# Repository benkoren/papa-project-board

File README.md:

# papa-project-board

This is a universal controller board, centered around the ESP32-C6-DevkitC-1-N8 development board. It is meant to be a solid jumping off point for microcontroller-oriented projects which justify the beefy features of the C6 devkit, including JTAG, 32-bit RISC-V MCU & 2.4 GHz Wi-Fi 6 & Bluetooth 5 (LE) & IEEE 802.15.4, etc.

(TODO: INSERT YOUTUBE DEMO LINK)

## PCB

This universal controller board in particular includes:
 - 1.3" OLED (which you can swap for other sizes as well)
 - (2) 12mm momentary push-button switches
 - rotary encoder switch
 - active buzzer
 - (2) dedicated connectors for 3-pin sensors (ex: DHT-22)
 - (2) dedicated connectors (and extra capacitance) for driving servo motors
 - TBD62783A chip for driving things like relays while protecting our MCU
 - LM2596T-5 voltage regulator that allows the board to be driven by anywhere between 6 and 45 volts (enabling the use of a wide variety of DC power supplies)
 - 10-pin JST-XH connectors are meant to be the primary interface to the usable GPIO pins of the MCU, though extra header pins are included to facilitate tinkering on the benchtop as well
 - 4-pin JSH-XH connector used to extend the I2C devices beyond the included OLED display

For the particular components & footprints, I chose sizes that are easy to install and maintain over the long-term - all Through Hole Technology (THT) components, and no Surface Mount Device (SMD). Silkscreens were heavily utilized so that the user does not need the schematic to populate and maintain the board - all information needed is printed right on the board.

The PCB design was done in KiCad - all relevant files are located in the `KiCad` folder.

The overall approach and many schematic choices borrow a great deal from the [Banano Board by Electro Bananas](https://www.youtube.com/watch?v=pLuV-ciUMUs) - much gratitude goes to him for his work.

## Enclosure

In addition to the PCB design, I've created a corresponding 3d-printed dashplate which allows the board to be incorporated into any surface mount style application.

One such application is the included "Enclosure Y", which is a small enclosure that orients the input components of the controller board up and toward the user, a rear plate where power supply and other connectors are intended to enter, and a bottom-plate which includes a 20mm grid which allows other components to be secured with included mount trays and M3 bolts.

The enclosure design was done in FreeCAD - all relevant files are located in the `FreeCAD` folder.

## Code

Perhaps just as important as the PCB itself is how it's driven: I've created a code template as a great starting point for all projects based upon the universal controller board. It supports some foundational things like driving the OLED and responding to the various inputs included with the board. It's in a separate repository here:

[Papa's Project Board - Code](https://github.com/benkoren/papa-project-board-code)

## Important Changes Across Revisions

### 1.0 to 1.1
 - C11 and C12 are now 0nF - they are counterproductive when using interrupts for SW2 and SW3. We're going to just use software debouncing instead. 
 - R8 is now 470R
 - R5 is now 4.7k (to dim the LED)
 - J7: Both pins 2 and 3 are now connected to GND

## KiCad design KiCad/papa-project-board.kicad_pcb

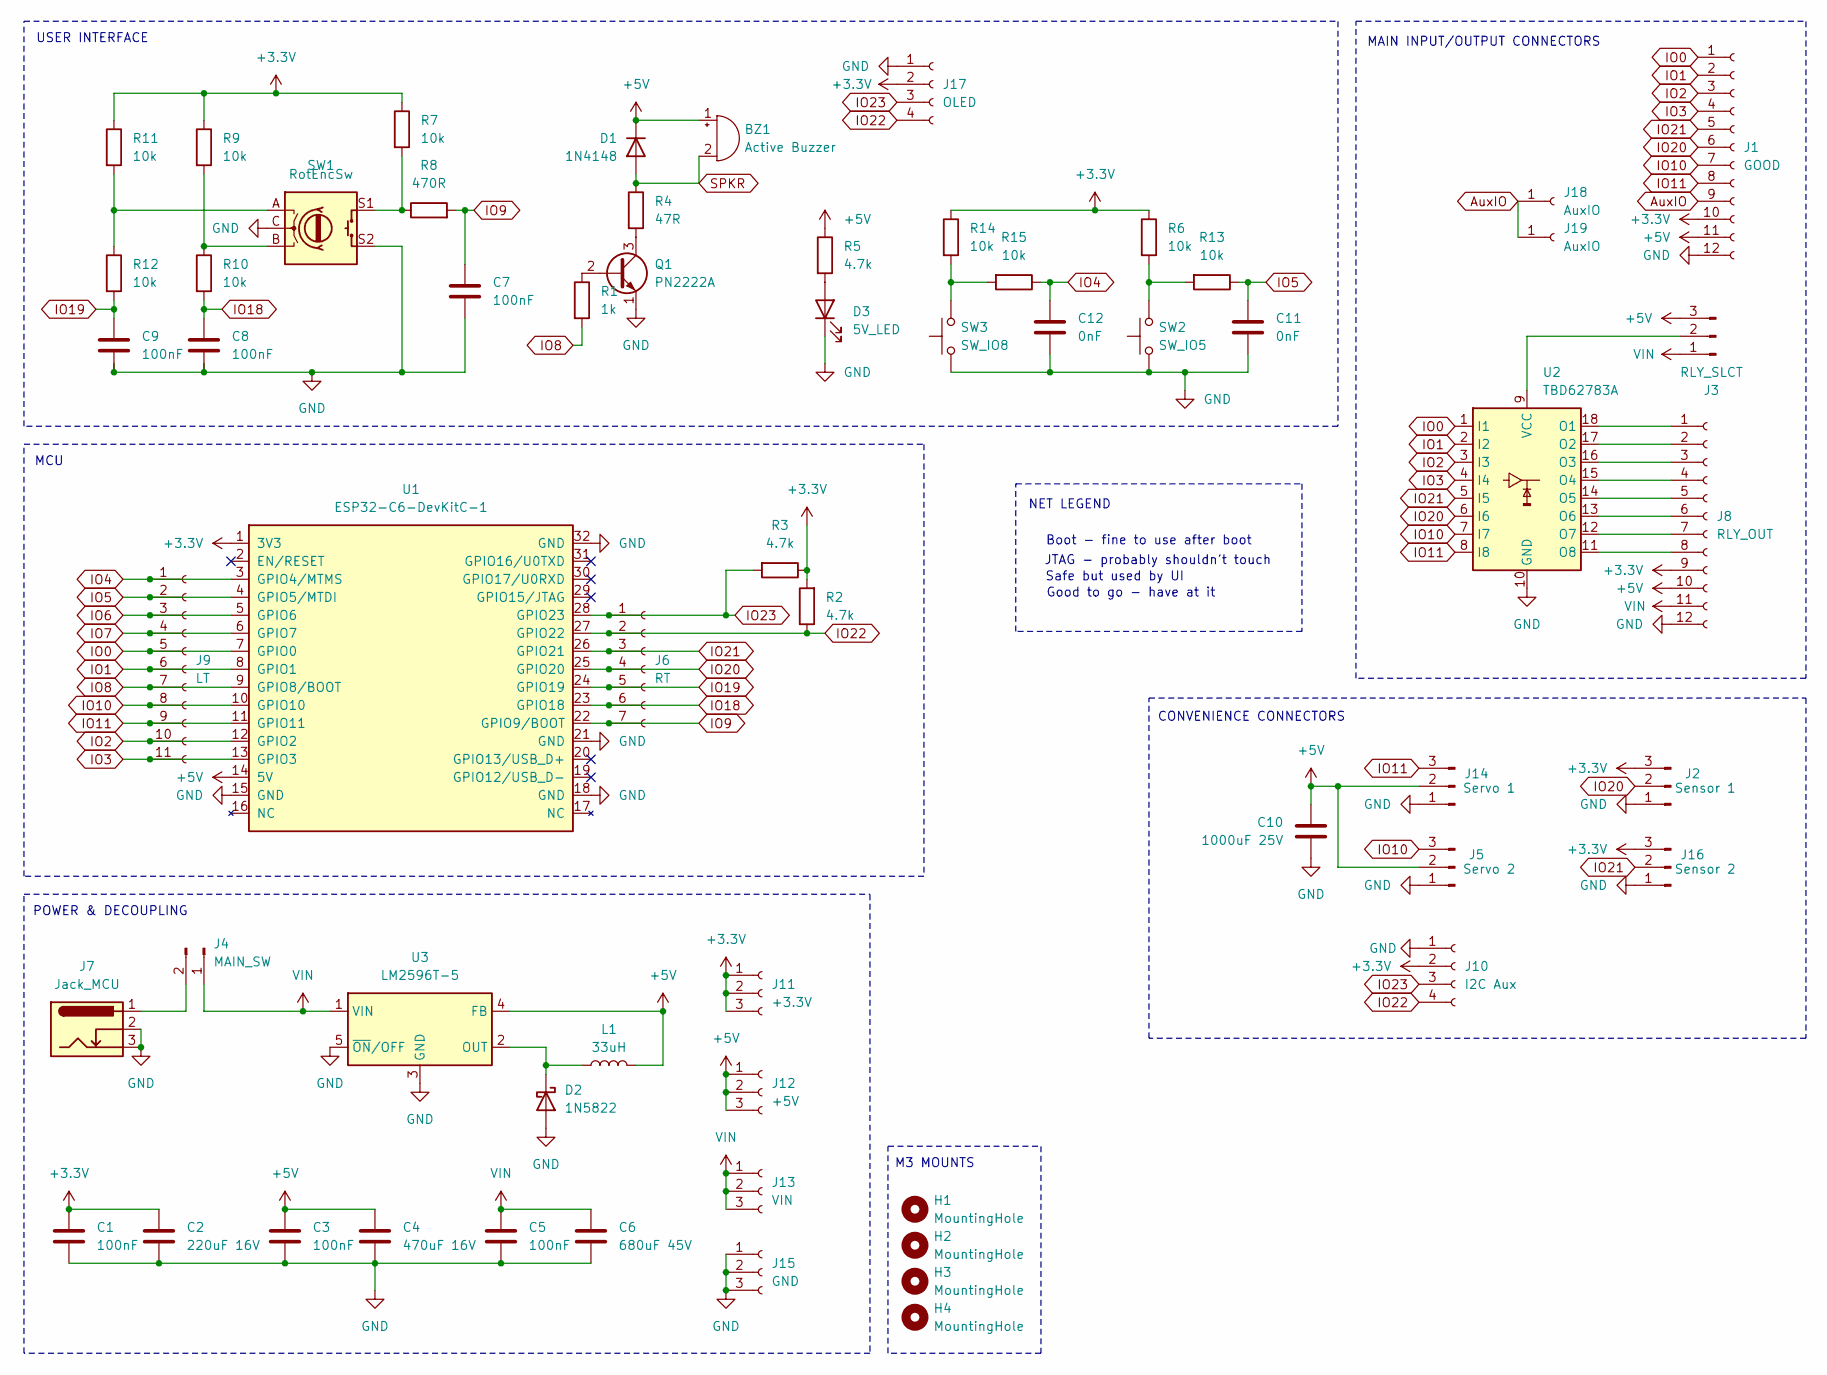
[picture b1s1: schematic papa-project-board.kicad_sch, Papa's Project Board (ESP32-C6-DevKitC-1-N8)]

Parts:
BZ1: Active Buzzer; Buzzer_12x9.5RM7.6
C1, C3, C5, C7, C8, C9: 100nF; C_Disc_D5.0mm_W2.5mm_P5.00mm
C2: 220uF 16V; CP_Radial_D8.0mm_P2.50mm
C4: 470uF 16V; CP_Radial_D8.0mm_P2.50mm
C6: 680uF 45V; CP_Radial_D8.0mm_P2.50mm
C10: 1000uF 25V; CP_Radial_D12.5mm_P5.00mm
C11, C12: 0nF; C_Disc_D5.0mm_W2.5mm_P5.00mm
D1: 1N4148; D_DO-35_SOD27_P7.62mm_Horizontal
D2: 1N5822; D_DO-201AD_P15.24mm_Horizontal
D3: 5V_LED; LED_D5.0mm
H1, H2, H3, H4: MountingHole; MountingHole_3.2mm_M3
J1: GOOD; JST_XH_B12B-XH-A_1x12_P2.50mm_Vertical
J2: Sensor 1; JST_XH_B3B-XH-A_1x03_P2.50mm_Vertical
J3: RLY_SLCT; PinHeader_1x03_P2.54mm_Vertical
J4: MAIN_SW; PinHeader_1x02_P2.54mm_Vertical
J5: Servo 2; JST_XH_B3B-XH-A_1x03_P2.50mm_Vertical
J6: RT; PinSocket_1x07_P2.54mm_Vertical
J7: Jack_MCU; BarrelJack_Horizontal
J8: RLY_OUT; JST_XH_B12B-XH-A_1x12_P2.50mm_Vertical
J9: LT; PinSocket_1x11_P2.54mm_Vertical
J10: I2C Aux; JST_XH_B4B-XH-A_1x04_P2.50mm_Vertical
J11: +3.3V; PinSocket_1x03_P2.54mm_Vertical
J12: +5V; PinSocket_1x03_P2.54mm_Vertical
J13: VIN; PinSocket_1x03_P2.54mm_Vertical
J14: Servo 1; JST_XH_B3B-XH-A_1x03_P2.50mm_Vertical
J15: GND; PinSocket_1x03_P2.54mm_Vertical
J16: Sensor 2; JST_XH_B3B-XH-A_1x03_P2.50mm_Vertical
J17: OLED; PinSocket_1x04_P2.54mm_Vertical
J18, J19: AuxIO; TestPoint_Pad_D1.0mm
L1: 33uH; L_Toroid_Vertical_L14.7mm_W8.6mm_P5.58mm_Pulse_KM-1
Q1: PN2222A; TO-92_Inline
R1: 1k; R_Axial_DIN0207_L6.3mm_D2.5mm_P10.16mm_Horizontal
R2, R3, R5: 4.7k; R_Axial_DIN0207_L6.3mm_D2.5mm_P10.16mm_Horizontal
R4: 47R; R_Axial_DIN0207_L6.3mm_D2.5mm_P10.16mm_Horizontal
R6, R7, R9, R10, R11, R12, R13, R14, R15: 10k; R_Axial_DIN0207_L6.3mm_D2.5mm_P10.16mm_Horizontal
R8: 470R; R_Axial_DIN0207_L6.3mm_D2.5mm_P10.16mm_Horizontal
SW1: RotEncSw; RotaryEncoder_Alps_EC11E-Switch_Vertical_H20mm
SW2: SW_IO5; SW_PUSH-12mm_Wuerth-430476085716
SW3: SW_IO8; SW_PUSH-12mm_Wuerth-430476085716
U1: ESP32-C6-DevKitC-1
U2: TBD62783A; DIP-18_W7.62mm_Socket
U3: LM2596T-5; TO-220-5_Vertical

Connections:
+3.3V: C1.1, C2.1, J1.10, J2.3, J8.9, J10.2, J11.1, J11.2, J11.3, J16.3, J17.2, R2.2, R3.1, R6.1, R7.1, R9.1, R11.1, R14.1, U1.1 (3V3)
+5V: BZ1.1 (+), C3.1, C4.1, C10.1, D1.1 (K), J1.11, J3.3, J5.2, J8.10, J12.1, J12.2, J12.3, J14.2, L1.2, R5.1, U1.14 (5V), U3.4 (FB)
AuxIO: J1.9, J18.1, J19.1
GND: C1.2, C2.2, C3.2, C4.2, C5.2, C6.2, C7.2, C8.2, C9.2, C10.2, C11.2, C12.2, D2.2 (A), D3.1 (K), J1.12, J2.1, J5.1, J7.2, J7.3, J8.12, J10.1, J14.1, J15.1, J15.2, J15.3, J16.1, J17.1, Q1.1 (E), SW1.C, SW1.S2, SW2.1, SW3.1, U1.15 (GND), U1.18 (GND), U1.21 (GND), U1.32 (GND), U2.10 (GND), U3.3 (GND), U3.5 (~ON/OFF)
IO0: J1.1, J9.5, U1.7 (GPIO0), U2.1 (I1)
IO1: J1.2, J9.6, U1.8 (GPIO1), U2.2 (I2)
IO2: J1.3, J9.10, U1.12 (GPIO2), U2.3 (I3)
IO3: J1.4, J9.11, U1.13 (GPIO3), U2.4 (I4)
IO4: C12.1, J9.1, R15.1, U1.3 (GPIO4/MTMS)
IO5: C11.1, J9.2, R13.1, U1.4 (GPIO5/MTDI)
IO6: J9.3, U1.5 (GPIO6)
IO7: J9.4, U1.6 (GPIO7)
IO8: J9.7, R1.2, U1.9 (GPIO8/BOOT)
IO9: C7.1, J6.7, R8.2, U1.22 (GPIO9/BOOT)
IO10: J1.7, J5.3, J9.8, U1.10 (GPIO10), U2.7 (I7)
IO11: J1.8, J9.9, J14.3, U1.11 (GPIO11), U2.8 (I8)
IO18: C8.1, J6.6, R10.2, U1.23 (GPIO18)
IO19: C9.1, J6.5, R12.2, U1.24 (GPIO19)
IO20: J1.6, J2.2, J6.4, U1.25 (GPIO20), U2.6 (I6)
IO21: J1.5, J6.3, J16.2, U1.26 (GPIO21), U2.5 (I5)
IO22: J6.2, J10.4, J17.4, R2.1, U1.27 (GPIO22)
IO23: J6.1, J10.3, J17.3, R3.2, U1.28 (GPIO23)
unnamed: D2.1 (K), L1.1, U3.2 (OUT)
unnamed: D3.2 (A), R5.2
unnamed: J3.2, U2.9 (VCC)
unnamed: J4.2, J7.1
unnamed: J8.1, U2.18 (O1)
unnamed: J8.2, U2.17 (O2)
unnamed: J8.3, U2.16 (O3)
unnamed: J8.4, U2.15 (O4)
unnamed: J8.5, U2.14 (O5)
unnamed: J8.6, U2.13 (O6)
unnamed: J8.7, U2.12 (O7)
unnamed: J8.8, U2.11 (O8)
unnamed: Q1.2 (B), R1.1
unnamed: Q1.3 (C), R4.2
unnamed: R7.2, R8.1, SW1.S1
unnamed: R9.2, R10.1, SW1.B
unnamed: R11.2, R12.1, SW1.A
unnamed: R6.2, R13.2, SW2.2
unnamed: R14.2, R15.2, SW3.2
SPKR: BZ1.2 (-), D1.2 (A), R4.1
VIN: C5.1, C6.1, J3.1, J4.1, J8.11, J13.1, J13.2, J13.3, U3.1 (VIN)

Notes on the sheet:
JTAG - probably shouldn't touch
USER INTERFACE
Boot - fine to use after boot
Good to go - have at it
MAIN INPUT/OUTPUT CONNECTORS
MCU
M3 MOUNTS
Safe but used by UI
NET LEGEND
POWER & DECOUPLING
CONVENIENCE CONNECTORS

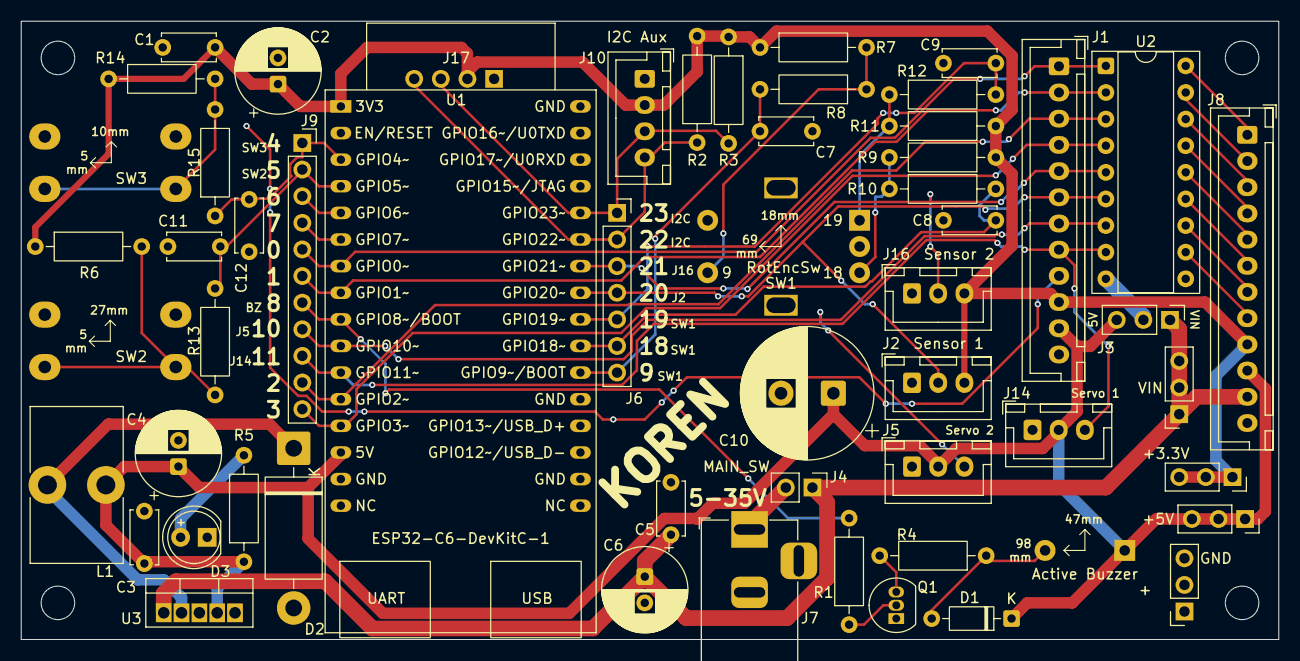
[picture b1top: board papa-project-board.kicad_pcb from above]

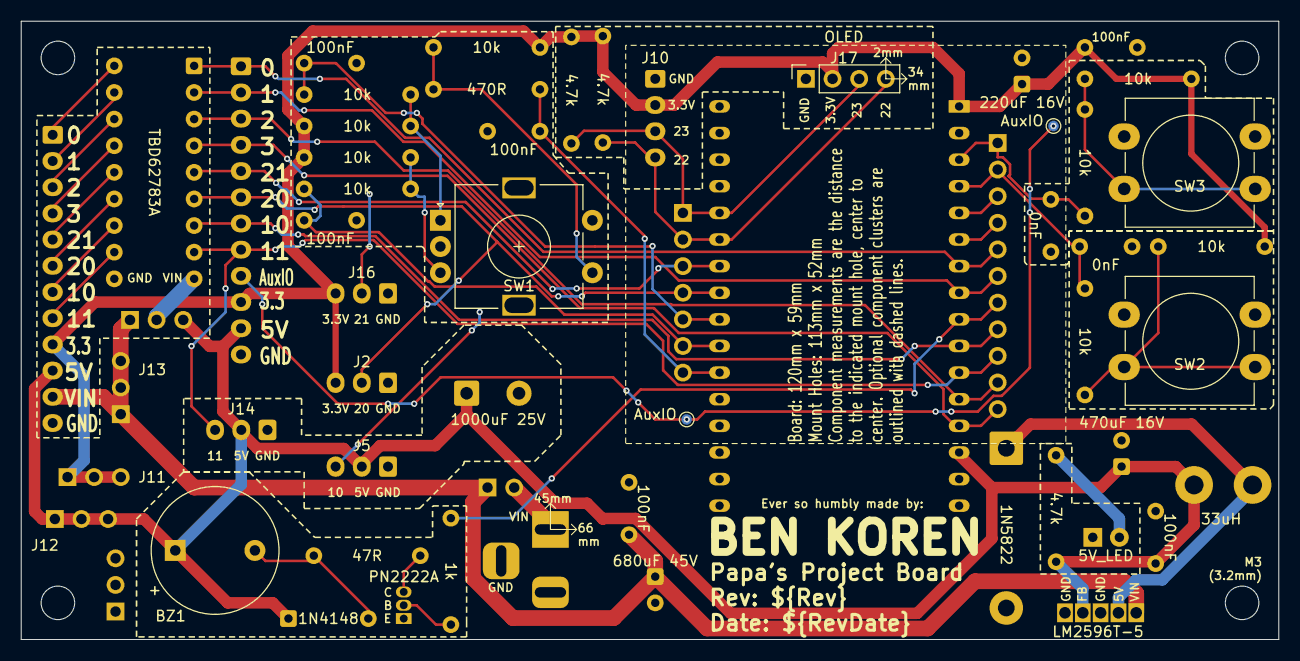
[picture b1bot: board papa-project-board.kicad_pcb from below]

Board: 2 copper layers, 120.0 x 59.0 mm, 62 parts (7 on the bottom side), 43 nets.

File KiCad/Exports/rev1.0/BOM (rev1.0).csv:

"Reference","Qty","Value","DNP","Exclude from BOM","Exclude from Board","Footprint","Datasheet"
"BZ1","1","Buzzer","","","","Buzzer_Beeper:Buzzer_D14mm_H7mm_P10mm","~"
"C1,C3,C5,C7,C8,C9,C11,C12","8","100nF","","","","Capacitor_THT:C_Disc_D5.0mm_W2.5mm_P5.00mm","~"
"C2","1","220uF 16V","","","","Capacitor_THT:CP_Radial_D8.0mm_P2.50mm","~"
"C4","1","470uF 16V","","","","Capacitor_THT:CP_Radial_D8.0mm_P2.50mm","~"
"C6","1","680uF 45V","","","","Capacitor_THT:CP_Radial_D8.0mm_P2.50mm","~"
"C10","1","1000uF 25V","","","","Capacitor_THT:CP_Radial_D12.5mm_P5.00mm","~"
"D1","1","1N4148","","","","Diode_THT:D_DO-35_SOD27_P7.62mm_Horizontal","https://assets.nexperia.com/documents/data-sheet/1N4148_1N4448.pdf"
"D2","1","1N5822","","","","Diode_THT:D_DO-201AD_P15.24mm_Horizontal","http://www.vishay.com/docs/88526/1n5820.pdf"
"D3","1","5V_LED","","","","LED_THT:LED_D5.0mm","~"
"H1,H2,H3,H4","4","MountingHole","","Excluded from BOM","","MountingHole:MountingHole_3.2mm_M3","~"
"J1","1","GOOD","","","","Connector_JST:JST_XH_B12B-XH-A_1x12_P2.50mm_Vertical","~"
"J2","1","Sensor 1","","","","Connector_JST:JST_XH_B3B-XH-A_1x03_P2.50mm_Vertical","~"
"J3","1","RLY_SLCT","","","","Connector_PinHeader_2.54mm:PinHeader_1x03_P2.54mm_Vertical","~"
"J4","1","MAIN_SW","","","","Connector_PinHeader_2.54mm:PinHeader_1x02_P2.54mm_Vertical","~"
"J5","1","Servo 2","","","","Connector_JST:JST_XH_B3B-XH-A_1x03_P2.50mm_Vertical","~"
"J6","1","RT","","","","Connector_PinSocket_2.54mm:PinSocket_1x07_P2.54mm_Vertical","~"
"J7","1","Jack_MCU","","","","Connector_BarrelJack:BarrelJack_Horizontal","~"
"J8","1","RLY_OUT","","","","Connector_JST:JST_XH_B12B-XH-A_1x12_P2.50mm_Vertical","~"
"J9","1","LT","","","","Connector_PinSocket_2.54mm:PinSocket_1x11_P2.54mm_Vertical","~"
"J10","1","I2C Aux","","","","Connector_JST:JST_XH_B4B-XH-A_1x04_P2.50mm_Vertical","~"
"J11","1","+3.3V","","","","Connector_PinSocket_2.54mm:PinSocket_1x03_P2.54mm_Vertical","~"
"J12","1","+5V","","","","Connector_PinSocket_2.54mm:PinSocket_1x03_P2.54mm_Vertical","~"
"J13","1","VIN","","","","Connector_PinSocket_2.54mm:PinSocket_1x03_P2.54mm_Vertical","~"
"J14","1","Servo 1","","","","Connector_JST:JST_XH_B3B-XH-A_1x03_P2.50mm_Vertical","~"
"J15","1","GND","","","","Connector_PinSocket_2.54mm:PinSocket_1x03_P2.54mm_Vertical","~"
"J16","1","Sensor 2","","","","Connector_JST:JST_XH_B3B-XH-A_1x03_P2.50mm_Vertical","~"
"J17","1","OLED","","","","Connector_PinSocket_2.54mm:PinSocket_1x04_P2.54mm_Vertical","~"
"J18,J19","2","AuxIO","","","","TestPoint:TestPoint_Pad_D1.0mm","~"
"L1","1","33uH","","","","Inductor_THT:L_Toroid_Vertical_L14.7mm_W8.6mm_P5.58mm_Pulse_KM-1","~"
"Q1","1","PN2222A","","","","Package_TO_SOT_THT:TO-92_Inline","https://www.onsemi.com/pub/Collateral/PN2222-D.PDF"
"R1","1","1k","","","","Resistor_THT:R_Axial_DIN0207_L6.3mm_D2.5mm_P10.16mm_Horizontal","~"
"R2,R3","2","4.7k","","","","Resistor_THT:R_Axial_DIN0207_L6.3mm_D2.5mm_P10.16mm_Horizontal","~"
"R4","1","47R","","","","Resistor_THT:R_Axial_DIN0207_L6.3mm_D2.5mm_P10.16mm_Horizontal","~"
"R5","1","330R","","","","Resistor_THT:R_Axial_DIN0207_L6.3mm_D2.5mm_P10.16mm_Horizontal","~"
"R6,R7,R8,R9,R10,R11,R12,R13,R14,R15","10","10k","","","","Resistor_THT:R_Axial_DIN0207_L6.3mm_D2.5mm_P10.16mm_Horizontal","~"
"SW1","1","RotEncSw","","","","Rotary_Encoder:RotaryEncoder_Alps_EC11E-Switch_Vertical_H20mm","~"
"SW2","1","SW_IO5","","","","Button_Switch_THT:SW_PUSH-12mm_Wuerth-430476085716","~"
"SW3","1","SW_IO8","","","","Button_Switch_THT:SW_PUSH-12mm_Wuerth-430476085716","~"
"U1","1","ESP32-C6-DevKitC-1","","","","PCM_Espressif:ESP32-C6-DevKitC-1","https://docs.espressif.com/projects/espressif-esp-dev-kits/e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"
"U2","1","TBD62783A","","","","Package_DIP:DIP-18_W7.62mm_Socket","http://toshiba.semicon-storage.com/info/docget.jsp?did=30523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"
"U3","1","LM2596T-5","","","","Package_TO_SOT_THT:TO-220-5_Vertical","http://www.ti.com/lit/ds/symlink/lm2596.pdf"

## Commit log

2026-02-09 Updated code repo link
2026-02-09 Added code preview
2026-02-10 Dimmed the power LED
2026-02-12 Increased size of Y enclosure, changed button facade style
2026-02-17 Added bus bar
2026-02-17 Added polarity text to bus bar
2026-02-19 Beefed up the rear plate
2026-02-19 Moved bottom plate mount bolts to the sides
2026-02-24 Fixed enclosure mount nut pockets
2026-02-24 Enclosure Y: bottom plate now rests within main body
2026-02-24 Fixed screenshot
